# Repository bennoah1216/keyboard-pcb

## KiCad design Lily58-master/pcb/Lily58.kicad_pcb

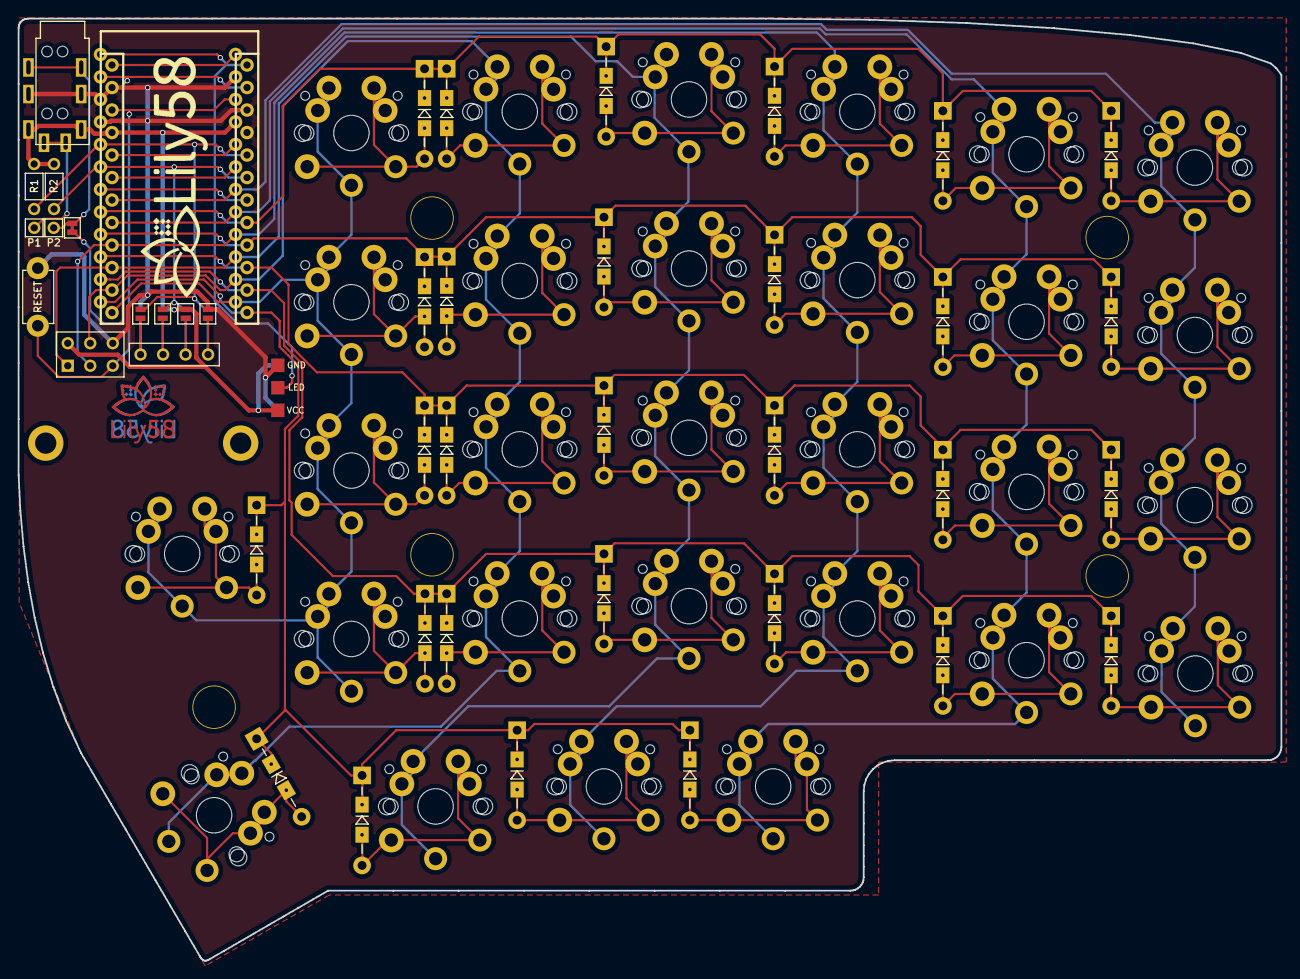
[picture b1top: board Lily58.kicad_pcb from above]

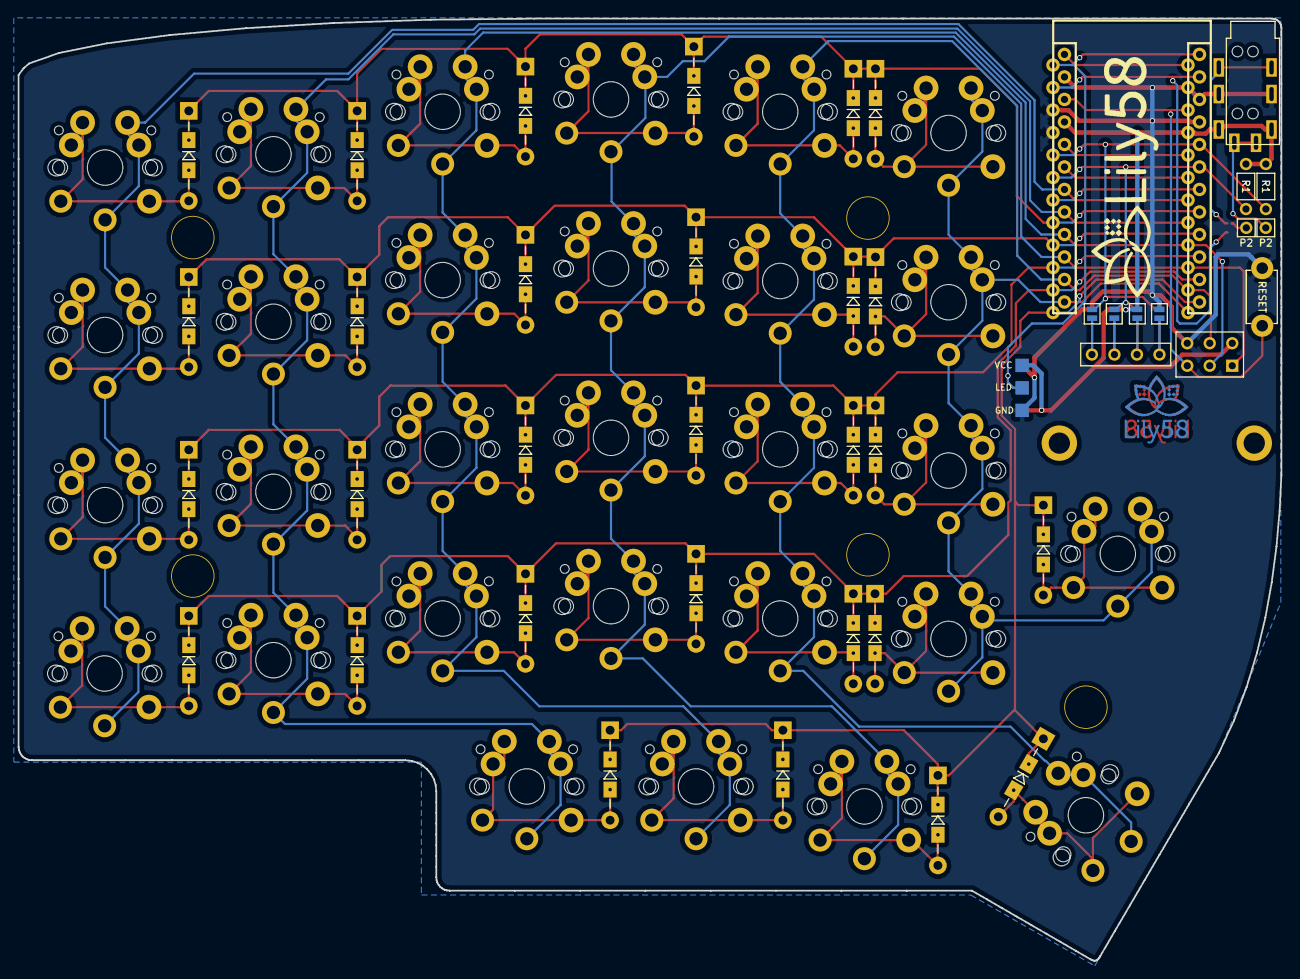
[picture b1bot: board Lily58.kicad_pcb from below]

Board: 2 copper layers, 142.5 x 106.3 mm, 84 parts (4 on the bottom side), 53 nets.

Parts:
D1, D2, D3, D4, D5, D6, D7, D8, D9, D10, D11, D12, D13, D14, D15, D16, D17, D18, D19, D20, D21, D22, D23, D24, D25, D26, D27, D28, D29: D; Diode_TH_SOD123
J1: LED; StripLED
J2: 4PIN; MJ-4PP-9
JP1, JP2, JP3, JP4, JP5, JP6, JP7, JP8: Jumper
OLED: OLED; MY_SIL-4
P1, P2: i2c_pin; 1pin_conn
P3: ICSP
R1, R2: R; RESISTOR_mini
RSW1: SW_RST; TACT_SWITCH_TVBP06
SW1, SW2, SW3, SW4, SW5, SW6, SW7, SW8, SW9, SW10, SW11, SW12, SW13, SW14, SW15, SW16, SW17, SW18, SW19, SW20, SW21, SW22, SW23, SW24, SW25, SW27, SW28, SW29: SW_PUSH; MX_PG1350-Under_FLIP_HOLES_18mm
SW26: SW_PUSH; MX_PG1350-Under_FLIP_HOLES_27mm
TH1, TH2: HOLE; M2_HOLE_PCB
TH3, TH4, TH5, TH6, TH7: HOLE; HOLE_M2_TH
U1: ProMicro; ProMicro_rev2
W1: jumper; jumper_data

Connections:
DATA: U1.2, W1.1
GND: J1.3, J2.2, JP1.2, JP8.2, P3.6, RSW1.1, U1.3, U1.4, U1.23
LED: J1.2, U1.1
unnamed: D1.2, SW1.2
unnamed: D2.2, SW2.2
unnamed: D3.2, SW3.2
unnamed: D4.2, SW4.2
unnamed: D5.2, SW5.2
unnamed: D6.2, SW6.2
unnamed: D7.2, SW7.2
unnamed: D8.2, SW8.2
unnamed: D9.2, SW9.2
unnamed: D10.2, SW10.2
unnamed: D11.2, SW11.2
unnamed: D12.2, SW12.2
unnamed: D13.2, SW13.2
unnamed: D14.2, SW14.2
unnamed: D15.2, SW15.2
unnamed: D16.2, SW16.2
unnamed: D17.2, SW17.2
unnamed: D18.2, SW18.2
unnamed: D19.2, SW19.2
unnamed: D20.2, SW20.2
unnamed: D21.2, SW21.2
unnamed: D22.2, SW22.2
unnamed: D23.2, SW23.2
unnamed: D24.2, SW24.2
unnamed: D25.2, SW25.2
unnamed: D26.2, SW26.2
unnamed: D27.2, SW27.2
unnamed: D28.2, SW28.2
unnamed: D29.2, SW29.2
unnamed: J2.3, P2.1, W1.2
unnamed: J2.4, P1.1
unnamed: JP1.1, JP5.1, OLED.4
unnamed: JP2.1, JP6.1, OLED.3
unnamed: JP3.1, JP7.1, OLED.2
unnamed: JP4.1, JP8.1, OLED.1
RESET: P3.5, RSW1.2, U1.22
SCL: JP3.2, JP6.2, R2.2, U1.6
SDA: JP4.2, JP5.2, R1.2, U1.5
VCC: J1.1, J2.1, JP2.2, JP7.2, P3.2, R1.1, R2.1, U1.21
col0: SW6.1, SW12.1, SW18.1, SW24.1, U1.18
col1: SW5.1, SW11.1, SW17.1, SW23.1, SW29.1, U1.17
col2: P3.3, SW4.1, SW10.1, SW16.1, SW22.1, SW28.1, U1.16
col3: P3.1, SW3.1, SW9.1, SW15.1, SW21.1, SW27.1, U1.15
col4: P3.4, SW2.1, SW8.1, SW14.1, SW20.1, SW26.1, U1.14
col5: SW1.1, SW7.1, SW13.1, SW19.1, SW25.1, U1.13
row0: D1.1, D2.1, D3.1, D4.1, D5.1, D6.1, U1.8
row1: D7.1, D8.1, D9.1, D10.1, D11.1, D12.1, U1.9
row2: D13.1, D14.1, D15.1, D16.1, D17.1, D18.1, U1.10
row3: D19.1, D20.1, D21.1, D22.1, D23.1, D24.1, U1.11
row4: D25.1, D26.1, D27.1, D28.1, D29.1, U1.12

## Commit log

2021-10-08 adding kicaid file
2021-10-08 Add submodules
2021-10-08 adding parts
2021-10-08 MCU build complete
2021-10-08 finished schema
2021-10-08 adding quefrency
2021-10-09 left pcb matrix done
2021-10-09 Right Matrix Finished
2021-10-09 add lily and other adjustments
2021-10-09 deleting unnecessary files
2021-10-10 updates to PCBs
